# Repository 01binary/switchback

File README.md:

<br>

<br>

<br>

Custom double-neck guitar design with keyboard for playing [neurometal](https://www.youtube.com/playlist?list=PL2ZwTvIdYJGJxl1kszP3a_z6O4DcHwvok).

* 6-string (bottom) modeled after [Strandberg Boden Metal 6](https://strandbergguitars.com/product/boden-metal-6-white-pearl/) with Fishman Fluence Modern 6 pickups
* 8-string (top) modeled after [Strandberg Boden Metal 8](https://www.sweetwater.com/store/detail/BDMT8BKP--strandberg-boden-metal-8-black-pearl) with Fishman Fluence Modern 8 pickups
* 9-key [Roli Seaboard Block keyboard](https://roli.com/products/seaboard) (bottom) with two extra dimensions of touch
* Built-in oscilloscope can display a waveform from a remote synth or sampler, similar to [Korg Minilogue](https://www.sweetwater.com/store/detail/MinilogueXD--korg-minilogue-xd-4-voice-analog-synthesizer)

|Content|In|
|-|-|
|Autodesk Inventor, AutoCAD|./src|
|Concept art and inspiration|./design|
|CAD Drawings|./design/cad|
|3D Renders|./design/render|
|References based on|./references|
|Export to various formats|./export|

<br>

<br>

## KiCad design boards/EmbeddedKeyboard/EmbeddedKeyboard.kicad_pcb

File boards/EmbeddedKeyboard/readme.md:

# Embedded MIDI Keyboard

A PCB embedded at the bottom of a custom guitar, with capacitive touch electrodes that function like keyboard keys. Touching keys sends MIDI messages over Bluetooth.

Each of the `13` keys is divided into `12` electrodes and functions like a capacitive touch slider, allowing the user to slide their finger up and down on each key to control MIDI "brightness" parameter (`CC74`).

> Note that the keyboard is mounted "upside down" for easy access when wearing the guitar.

## Overview

+ All MIDI messages are sent on channel `1`
+ Touching any electrode of a key will send a MIDI `Note On` message with maximum velocity and the note value set according to the key index
+ When touch is no longer registered on a key, the controller will send a MIDI `Note Off` message with minimum velocity
+ The system is strictly **monophonic**:
  - At most one key may be active at any time
  - At most one electrode position is considered active at any time
+ Depending on which key electrode was touched (`0` through `23`), the controller will send a `Control Change` message with controller `74` (or `4AH`, mapped to *brightness* in MIDI specification) and value equal to the index of the key electrode mapped onto `0` through `127` range.

The board outline is provided as an `.svg` export. This includes the shape of the board, hole placement, and the shape of the electrodes:

The capacitive touch electrodes must be placed on one side of the board, and all components on the other.

## Requirements

### General
- All MIDI messages are sent on channel `1`
- MIDI Control Change `CC74` (`0x4A`, Brightness) is always sent when a key is touched or released
- Control Change value is derived from the closest electrode index (`0–11`) mapped linearly to `0–127`

### Touch behavior

#### Case 1: Touch a key when no other key is active

+ Given my finger is over the `C1` key
+ When I touch any electrode within this key
  - Then the controller sends **MIDI Control Change**
    * Channel: `1`
    * Controller: `CC74`
    * Value: `0–127` (mapped from electrode index)
  - Then the controller sends **MIDI Note On**
    * Channel: `1`
    * Pitch: `C1`
    * Velocity: `127`

#### Case 2: Move to another key while holding a key

+ Given I am holding the `C1` key
+ When I touch any electrode within the `C2` key
  - Then the controller sends **MIDI Note Off**
    * Channel: `1`
    * Pitch: `C1`
    * Velocity: `0`
  - Then the controller sends **MIDI Control Change**
    * Channel: `1`
    * Controller: `CC74`
    * Value: `0–127` (mapped from electrode index)
  - Then the controller sends **MIDI Note On**
    * Channel: `1`
    * Pitch: `C2`
    * Velocity: `127`

#### Case 3: Release the active key

+ When I release the active key
  - Then the controller sends **MIDI Control Change**
    * Channel: `1`
    * Controller: `CC74`
    * Value: `0–127`
  - Then the controller sends **MIDI Note Off**
    * Channel: `1`
    * Pitch: last active pitch
    * Velocity: `0`

## Testing

[MIDI Monitor](https://www.snoize.com/MIDIMonitor/) can be used for testing this device once assembled to ensure it adheres to above requirements.

## Architecture

### Controller

The [ESP32-S3-DEVKITC-1-N8](https://www.digikey.com/en/products/detail/espressif-systems/ESP32-S3-DEVKITC-1-N8/15199021) controller was chosen because it can function like a Bluetooth MIDI device, and it's also used for the embedded oscilloscope board in the same project.

The ESP32-S3 shall expose all required GPIO, I²C, UART, boot, and reset signals on the PCB without relying on bodge wires.

### Capacitive Touch

The [MPR121QR2](https://www.digikey.com/en/products/detail/nxp-usa-inc/MPR121QR2/2186527) capacitive touch controller was selected due to its simplicity, reliability, and native I²C interface. Each MPR121 provides **12 capacitive electrodes**, and multiple devices can coexist on the same I²C bus using its **four selectable I²C addresses (0x5A–0x5D)**.

This project requires **13 keys × 12 electrodes per key = 156 total electrodes**, corresponding to **13 MPR121 devices** (1 per key).

To minimize device count, routing complexity, and I²C bus capacitance, the design shall use a **single [TCA9548A](https://www.digikey.com/en/products/detail/texas-instruments/tca9548apwr/3615458) I²C multiplexer**. Each TCA9548A downstream channel may host **up to four MPR121 devices**, differentiated by their I²C addresses. With this approach, all 13 MPR121 devices can be supported using **7 of the 8 available TCA9548A channels**, leaving one channel unused for expansion or debugging.

This architecture is preferred over a "one-sensor-per-mux-channel" approach because it:

- Minimizes the number of multiplexers
- Reduces PCB routing congestion
- Keeps I²C timing deterministic
- Simplifies firmware scanning (each sensor is read once per scan cycle)

Each key shall be treated logically as a **1D capacitive slider**, composed of **12 contiguous electrodes**, with position derived in firmware from the combined electrode state.

> Note: each MPR121 device has an IRQ (interrupt) pin pulled `LOW` when touch is registered.

### Power

This section is a **direct reuse** of a previously validated "Embedded Oscilliscope" design and should not be functionally modified unless required for layout reasons.

A [USB-C](https://www.digikey.com/en/products/detail/hirose-electric-co-ltd/CX90B1-24P/8769505) receptacle is used to program the board, providing power during the programming process. Two [TS-1064S-A1B2-D4](https://www.lcsc.com/product-detail/C498294.html?s_z=n_C498294) switches (boot and reset) are used for manual programming. A [DMN3135LVT-7](https://www.digikey.com/en/products/detail/diodes-incorporated/dmn3135lvt-7/2890874) MOSTFET enables automatic programming from Arduino IDE.

The circuitry from [Adafruit LiPo backpack](https://www.adafruit.com/product/2124) is integrated directly onto the board to provide power from a LiPo battery after the device is programmed. This includes [S2B-PH-SM4-TB](https://www.digikey.com/en/products/detail/jst-sales-america-inc/s2b-ph-sm4-tb/926655) **battery connector** and a **sliding power switch**. If the battery is connected while power is provided to the USB-C connector, this also charges the battery.

The power switch (connected to LiPo Battery Backpack circuit) is **external** for this project - but [S2B-PH-SM4-TB](https://www.digikey.com/en/products/detail/jst-sales-america-inc/s2b-ph-sm4-tb/926655) connector will be needed on the board to connect this external switch in a modular fashion. This is exactly the same connector as the one used for the battery.

The circuitry from [Adafruit LM3671 Buck Converter](https://www.adafruit.com/product/2745) is integrated directly onto the board to convert the battery voltage to `3.3V` required for the controller and all other components.

## Components

|Component|Description|
|-|-|
|[ESP32-WROOM-32E-N4](https://www.lcsc.com/product-detail/C701341.html)|Controller|
|[MCP73831T-2ACI/OT](https://www.digikey.com/en/products/detail/microchip-technology/mcp73831t-2aci-ot/964301)|Battery Charger
|[150080SS75000](https://www.digikey.com/en/products/detail/w-rth-elektronik/150080SS75000/4489919)|Red LED
|[150080GS75000](https://www.digikey.com/en/products/detail/w-rth-elektronik/150080GS75000/4489913)|Green LED
|[RE0805FRE071KL](https://www.digikey.com.au/en/products/detail/yageo/RE0805FRE071KL/5923534)|1K Resistor
|[RC0805FR-072K49L](https://www.digikey.com/en/products/detail/yageo/RC0805FR-072K49L/727695)|2.5K Resistor
|[0402WGF5101TCE](https://www.lcsc.com/product-detail/C25905.html)|5.1K Resistor
|[AF0805FR-0710KL](https://www.digikey.it/en/products/detail/yageo/AF0805FR-0710KL/5901208)|10K Resistor
|[RT0805FRE0775KL](https://www.digikey.com/en/products/detail/yageo/RT0805FRE0775KL/1079396)|75K Resistor
|[RC0805FR-07100KL](https://www.digikey.com/en/products/detail/yageo/RC0805FR-07100KL/727544)|100K Resistor
|[RTT01513JTH](https://www.lcsc.com/product-detail/C102736.html)|51K Resistor
|[0805W8F220JT5E](https://jlcpcb.com/partdetail/18249-0805W8F220JT5E/C17561)|22 Ohm Resistor
|[S2B-PH-SM4-TB](https://www.digikey.com/en/products/detail/jst-sales-america-inc/S2B-PH-SM4-TB/926655)|LiPo Battery Connector, Power Switch Connector
|[CC0805KKX5R5BB106](https://www.digikey.com/en/products/detail/yageo/cc0805kkx5r5bb106/2833624)|10uF Capacitor
|[CC0805MKX5R5BB226](https://www.digikey.com/en/products/detail/yageo/CC0805MKX5R5BB226/2833629)|22uF Capacitor
|[CL03A104KP3NNNC](https://www.digikey.com/en/products/detail/samsung-electro-mechanics/cl03a104kp3nnnc/3886773)|100nF Capacitor
|[LM3671MFX-3.3/NOPB](https://www.digikey.com/en/products/detail/texas-instruments/LM3671MFX-3.3-NOPB/6597333)|3.3V DC-DC Buck Converter
|[NRH2412T2R2MNGH](https://www.digikey.com/en/products/detail/taiyo-yuden/NRH2412T2R2MNGH/4157831)|2.2uH Inductor
|[TS-1064S-A1B2-D4](https://www.lcsc.com/product-detail/C498294.html)|Boot and Reset Switches
|[USB-C31-S-RA-CS2-SMT-BK-T/R](https://www.digikey.com/en/products/detail/adam-tech/USB-C31-S-RA-CS2-SMT-BK-T-R/9833235)|USB-C Receptacle
|[DMN3135LVT-7](https://www.digikey.com/en/products/detail/diodes-incorporated/dmn3135lvt-7/2890874)|ESP32 Auto-program MOSFET
|[CH340C](https://www.lcsc.com/product-detail/C84681.html)|USB to Serial Converter
|[MPR121QR2](https://www.digikey.com/en/products/detail/nxp-usa-inc/mpr121qr2/2186527)|Capacitive Touch Sensor
|[TCA9548APWR](https://www.digikey.com/en/products/detail/texas-instruments/tca9548apwr/3615458)|I2C Multiplexer (Bus Switch)

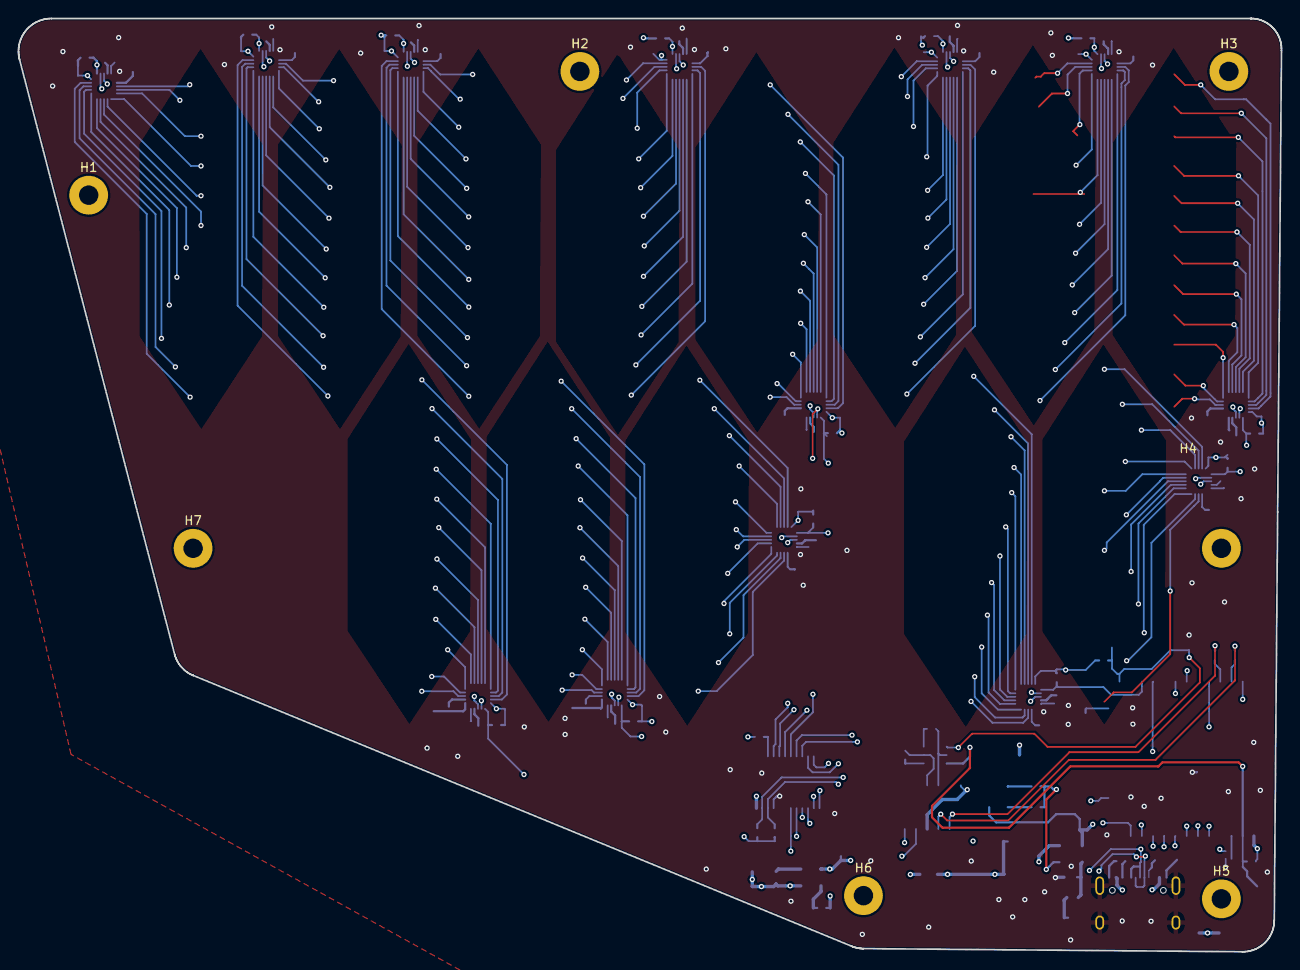
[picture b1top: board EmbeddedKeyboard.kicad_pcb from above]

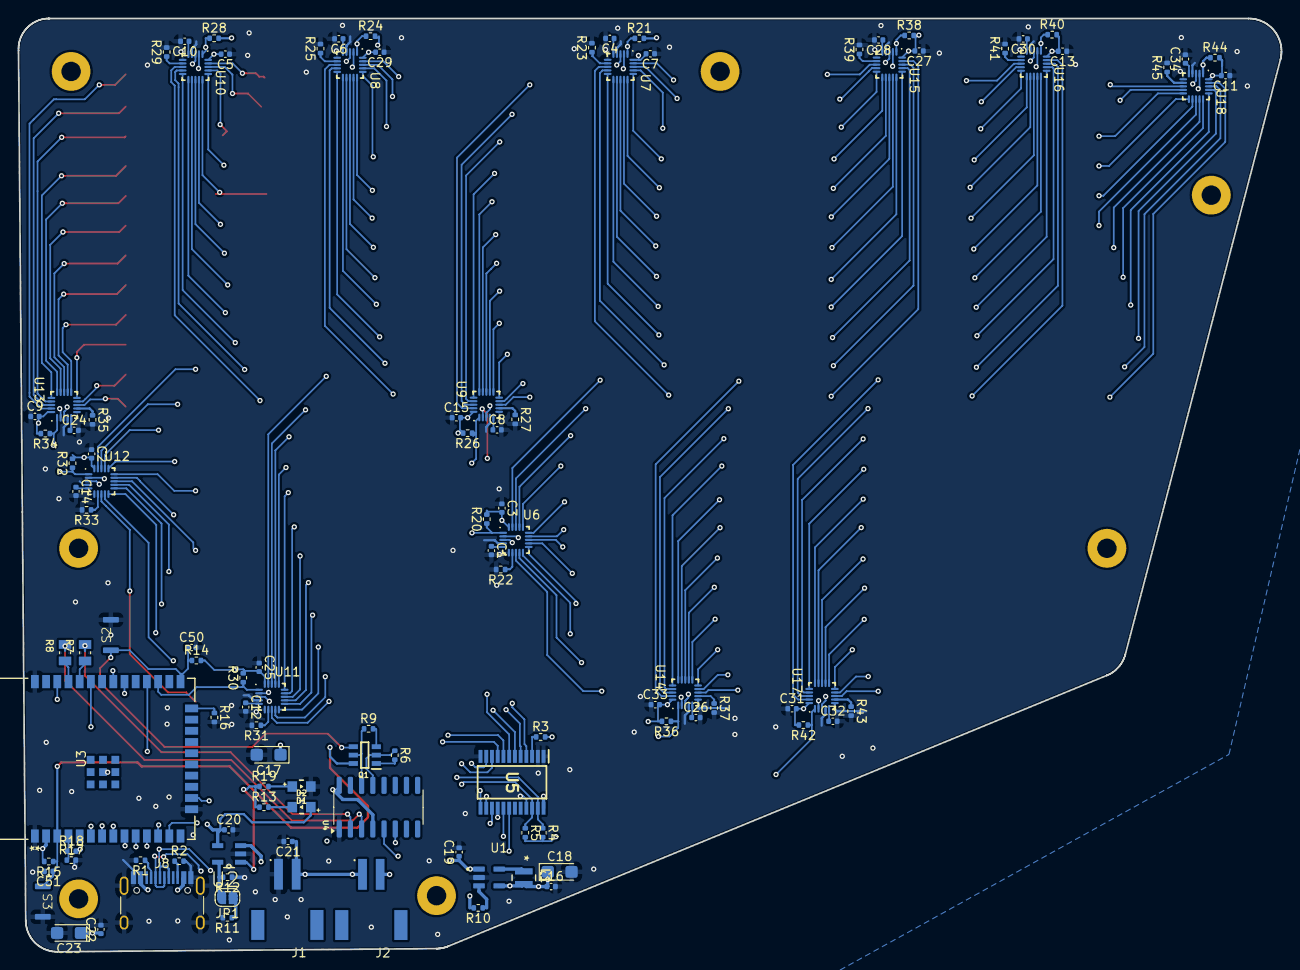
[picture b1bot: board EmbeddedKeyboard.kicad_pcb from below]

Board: 4 copper layers, 143.2 x 105.8 mm, 116 parts (109 on the bottom side), 84 nets.

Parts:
C1, C2, C3, C4, C5, C6, C7, C8, C9, C10, C11, C12, C13, C14, C15, C16, C22, C24, C25, C26, C27, C28, C29, C30, C31, C32, C33, C34, C50, C51: 100nF; C_0402_1005Metric
C17, C18, C23: 10uF; CP_EIA-3216-18_Kemet-A
C19, C20, C21: 10uF; C_0402_1005Metric
D1: GREEN LED (DONE); 150080GS75000
D2: RED LED (CHARGING); 150080SS75000
H1, H2, H3, H4, H5, H6, H7: MountingHole; MountingHole_2.2mm_M2_Pad
J1: S2B-PH-SM4-TB
J2: EXTERNAL SWITCH; S2B-PH-SM4-TB
J8: USB_C_Receptacle_USB2.0_14P; USB_C_Receptacle_HRO_TYPE-C-31-M-12
JP1: SolderJumper; SolderJumper-2_P1.3mm_Open_RoundedPad1.0x1.5mm
L1: 2.2uH; NRH2412T2R2MNGH
Q1: DMN3135LVT-7
R1, R2: 5.1k; R_0402_1005Metric
R3, R4, R5, R6, R9, R12, R14, R15, R16, R20, R21, R24, R26, R28, R30, R32, R34, R36, R38, R40, R42, R44: 10K; R_0402_1005Metric
R7, R8: 22R; 0805W8F220JT5E
R10: 100K; R_0402_1005Metric
R11: 2.5K; R_0402_1005Metric
R13, R19: 1K; R_0402_1005Metric
R17, R18: 51K; R_0402_1005Metric
R22, R23, R25, R27, R29, R31, R33, R35, R37, R39, R41, R43, R45: 75K; R_0402_1005Metric
S2, S3: TS-1064S-A1B2-D4
U1: LM3671MFX-3.3_NOPB; SOT95P280X145-5N
U2: MCP73831T-2ACI_OT; MCP73831T-2ACI-OT
U3: ESP32-WROOM-32E; ESP32-WROOM-32E-N4
U4: CH340C
U5: TCA9548APWR; SOP65P640X120-24N
U6, U7, U8, U9, U10, U11, U12, U13, U14, U15, U16, U17, U18: MPR121QR2

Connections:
+3.3V: C2.2, C3.2, C5.2, C7.2, C9.2, C11.2, C13.2, C15.2, C16.1, C17.1, C18.1, C25.2, C27.2, C29.2, C31.2, C33.2, L1.2, R3.2, R4.2, R5.2, R14.2, R15.2, R20.2, R21.2, R24.2, R26.2, R28.2, R30.2, R32.2, R34.2, R36.2, R38.2, R40.2, R42.2, R44.2, U1.4 (FB), U3.2 (VDD), U4.4 (V3), U4.16 (VCC), U5.24 (VCC), U6.20 (VDD), U7.20 (VDD), U8.20 (VDD), U9.20 (VDD), U10.20 (VDD), U11.20 (VDD), U12.20 (VDD), U13.20 (VDD), U14.20 (VDD), U15.20 (VDD), U16.20 (VDD), U17.20 (VDD), U18.20 (VDD)
+5V: C20.1, C22.1, C23.1, D2.2, J8.A4 (VBUS), J8.A9 (VBUS), J8.B4 (VBUS), J8.B9 (VBUS), U2.4 (VDD)
/Bat: R17.1, R18.1, U3.4 (SENSOR_VP)
/D+: J8.A6 (D+), J8.B6 (D+), U4.5 (UD+)
/D-: J8.A7 (D-), J8.B7 (D-), U4.6 (UD-)
/DTR: Q1.2 (S2), R6.1, U4.13 (~DTR)
/G0: C50.1, Q1.4 (D2), R14.1, S2.1, U3.25 (IO0)
/G2: R16.1, U3.24 (IO2)
/RTS: Q1.5 (S1), R9.1, U4.14 (~RTS)
/Rst: C51.1, Q1.6 (D1), R15.1, S3.1, U3.3 (EN)
/URx: R7.1, U3.34 (RXD0/IO3)
/UTx: R8.1, U3.35 (TXD0/IO1)
GND: C1.2, C2.1, C3.1, C4.2, C5.1, C6.2, C7.1, C8.2, C9.1, C10.2, C11.1, C12.2, C13.1, C14.2, C15.1, C16.2, C17.2, C18.2, C19.2, C20.2, C21.2, C22.2, C23.2, C24.2, C25.1, C26.2, C27.1, C28.2, C29.1, C30.2, C31.1, C32.2, C33.1, C34.2, C50.2, C51.2, D1.1, J1.1, J8.A1 (GND), J8.A12 (GND), J8.B1 (GND), J8.B12 (GND), J8.S1 (SHIELD), R1.2, R2.2, R11.2, R12.1, R16.2, R17.2, R22.2, R23.2, R25.2, R27.2, R29.2, R31.2, R33.2, R35.2, R37.2, R39.2, R41.2, R43.2, R45.2, S2.2, S3.2, U1.2 (GND), U2.2 (VSS), U3.1 (GND), U3.15 (GND), U3.38 (GND), U3.39 (GND), U4.1 (GND), U5.1 (A0), U5.2 (A1), U5.12 (GND), U5.21 (A2), U6.4 (ADDR), U6.6 (VSS), U7.4 (ADDR), U7.6 (VSS), U8.4 (ADDR), U8.6 (VSS), U9.4 (ADDR), U9.6 (VSS), U10.4 (ADDR), U10.6 (VSS), U11.4 (ADDR), U11.6 (VSS), U12.4 (ADDR), U12.6 (VSS), U13.4 (ADDR), U13.6 (VSS), U14.4 (ADDR), U14.6 (VSS), U15.4 (ADDR), U15.6 (VSS), U16.4 (ADDR), U16.6 (VSS), U17.4 (ADDR), U17.6 (VSS), U18.4 (ADDR), U18.6 (VSS)
I2C_RESET_IN: R3.1, U5.3 (*RESET)
IRQ0: R20.1, U3.28 (IO17), U6.1 (~IRQ)
IRQ1: R21.1, U3.12 (IO27), U7.1 (~IRQ)
IRQ2: R24.1, U3.31 (IO19), U8.1 (~IRQ)
IRQ3: R26.1, U3.30 (IO18), U9.1 (~IRQ)
IRQ4: R28.1, U3.8 (IO32), U10.1 (~IRQ)
IRQ5: R30.1, U3.27 (IO16), U11.1 (~IRQ)
IRQ6: R32.1, U3.7 (IO35), U12.1 (~IRQ)
IRQ7: R34.1, U3.6 (IO34), U13.1 (~IRQ)
IRQ8: R36.1, U3.16 (IO13), U14.1 (~IRQ)
IRQ9: R38.1, U3.13 (IO14), U15.1 (~IRQ)
IRQ10: R40.1, U3.11 (IO26), U16.1 (~IRQ)
IRQ11: R42.1, U3.10 (IO25), U17.1 (~IRQ)
IRQ12: R44.1, U3.9 (IO33), U18.1 (~IRQ)
unnamed: D1.2, R19.2
unnamed: D2.1, R13.2
unnamed: J8.A5 (CC1), R1.1
unnamed: J8.B5 (CC2), R2.1
unnamed: JP1.1 (A), R11.1
unnamed: JP1.2 (B), R12.2, U2.5 (PROG)
unnamed: Q1.1 (G1), R6.2
unnamed: Q1.3 (G2), R9.2
unnamed: R10.1, U1.3 (EN)
unnamed: L1.1, U1.5 (SW)
unnamed: R13.1, R19.1, U2.1 (STAT)
unnamed: R8.2, U4.3 (RXD)
unnamed: R7.2, U4.2 (TXD)
unnamed: R22.1, U6.7 (REXT)
unnamed: C1.1, U6.5 (VREG)
unnamed: R23.1, U7.7 (REXT)
unnamed: C4.1, U7.5 (VREG)
unnamed: R25.1, U8.7 (REXT)
unnamed: C6.1, U8.5 (VREG)
unnamed: R27.1, U9.7 (REXT)
unnamed: C8.1, U9.5 (VREG)
unnamed: R29.1, U10.7 (REXT)
unnamed: C10.1, U10.5 (VREG)
unnamed: R31.1, U11.7 (REXT)
unnamed: C12.1, U11.5 (VREG)
unnamed: R33.1, U12.7 (REXT)
unnamed: C14.1, U12.5 (VREG)
unnamed: R35.1, U13.7 (REXT)
unnamed: C24.1, U13.5 (VREG)
unnamed: R37.1, U14.7 (REXT)
unnamed: C26.1, U14.5 (VREG)
unnamed: R39.1, U15.7 (REXT)
unnamed: C28.1, U15.5 (VREG)
unnamed: R41.1, U16.7 (REXT)
unnamed: C30.1, U16.5 (VREG)
unnamed: R43.1, U17.7 (REXT)
unnamed: C32.1, U17.5 (VREG)
unnamed: R45.1, U18.7 (REXT)
unnamed: C34.1, U18.5 (VREG)
SCL0: U5.5 (SC0), U6.2 (SCL), U7.2 (SCL)
SCL1: U5.7 (SC1), U8.2 (SCL), U9.2 (SCL)
SCL2: U5.9 (SC2), U10.2 (SCL), U11.2 (SCL)
SCL3: U5.11 (SC3), U12.2 (SCL), U13.2 (SCL)
SCL4: U5.14 (SC4), U14.2 (SCL), U15.2 (SCL)
SCL5: U5.16 (SC5), U16.2 (SCL), U17.2 (SCL)
SCL6: U5.18 (SC6), U18.2 (SCL)
SCL_IN: R5.1, U3.36 (IO22), U5.22 (SCL)
SDA0: U5.4 (SD0), U6.3 (SDA), U7.3 (SDA)
SDA1: U5.6 (SD1), U8.3 (SDA), U9.3 (SDA)
SDA2: U5.8 (SD2), U10.3 (SDA), U11.3 (SDA)
SDA3: U5.10 (SD3), U12.3 (SDA), U13.3 (SDA)
SDA4: U5.13 (SD4), U14.3 (SDA), U15.3 (SDA)
SDA5: U5.15 (SD5), U16.3 (SDA), U17.3 (SDA)
SDA6: U5.17 (SD6), U18.3 (SDA)
SDA_IN: R4.1, U3.33 (IO21), U5.23 (SDA)
VB+: C21.1, J1.2, J2.1, U2.3 (VBAT)
VBo+: C19.1, J2.2, R10.2, R18.2, U1.1 (VIN)

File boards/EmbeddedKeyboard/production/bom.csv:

Designator,Footprint,Quantity,Value,LCSC Part #
"C1, C10, C11, C12, C13, C14, C15, C16, C2, C22, C24, C25, C26, C27, C28, C29, C3, C30, C31, C32, C33, C34, C4, C5, C50, C51, C6, C7, C8, C9",0402,30,100nF,C1525 
"C17, C18, C23",CP_EIA-3216-18_Kemet-A,3,10uF,C7171
"C19, C20, C21",0402,3,10uF,C77000
D1,150080GS75000,1,GREEN LED (DONE),C12624
D2,150080SS75000,1,RED LED (CHARGING),C2286
J1,S2B-PH-SM4-TB,1,S2B-PH-SM4-TB,C51940124
J2,S2B-PH-SM4-TB,1,EXTERNAL SWITCH,C51940124
J8,USB_C_Receptacle_HRO_TYPE-C-31-M-12,1,USB_C_Receptacle_USB2.0_14P,C165948 
L1,NRH2412T2R2MNGH,1,2.2uH,C89149 
Q1,DMN3135LVT-7,1,DMN3135LVT-7,C155326 
"R1, R2",0402,2,5.1k,C25905 
R10,0402,1,100K,C25741
R11,0402,1,2.5K,C25884
"R12, R14, R15, R16, R20, R21, R24, R26, R28, R3, R30, R32, R34, R36, R38, R4, R40, R42, R44, R5, R6, R9",0402,22,10K,C25744
"R13, R19",0402,2,1K,C11702
"R17, R18",0402,2,51K,C25794 
"R22, R23, R25, R27, R29, R31, R33, R35, R37, R39, R41, R43, R45",0402,13,75K,C25798
"R7, R8",0402,2,22R,C17561 
"S2, S3",TS-1064S-A1B2-D4,2,TS-1064S-A1B2-D4,C498294
U1,SOT95P280X145-5N,1,LM3671MFX-3.3_NOPB,C477918
"U10, U11, U12, U13, U14, U15, U16, U17, U18, U6, U7, U8, U9",MPR121QR2,13,MPR121QR2,C91322
U2,MCP73831T-2ACI-OT,1,MCP73831T-2ACI_OT,C424093
U3,ESP32-WROOM-32E-N4,1,ESP32-WROOM-32E,C328062 
U4,CH340C,1,CH340C,C84681
U5,SOP65P640X120-24N,1,TCA9548APWR,C130026

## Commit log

2018-01-20 Initial concepts
2018-01-20 Update images add specs
2018-01-20 Add 9-string specs
2018-01-20 Add references
2018-01-28 Developing vector outline
2018-01-28 Finalize outline 2
2018-01-30 Updated and exported outline2
2018-03-26 Adjust outline2
2019-05-31 add more designs
2019-06-01 Last updates before CAD
2019-12-05 Updated after sending to 3D CNC
2019-12-29 another iteration after proto
2019-12-30 Add drawings and 3D
2019-12-30 Update exports
2019-12-30 Export with dimensions
2020-01-15 parts, assembly, more refs and design
2020-01-15 separated wood pieces
2020-01-16 divide and fillets
2020-01-17 add todo
2020-01-17 add neck profiles
2020-01-17 verify neck mounts and lofts
2020-01-19 Defined neck mounts more
2020-01-19 head and neck detailing
2020-01-21 Adding block
2020-01-21 seaboard detail
2020-01-21 finished seaboard, repairing body
2020-01-22 redoing compartments
2020-01-23 block ifeatures
2020-01-23 working on cavities again:
2020-01-25 more work on compartments
2020-01-25 redoing control mounts
2020-01-28 Revalidate after indent adjustment
2020-01-28 Lengthened neck bases
2020-01-28 Update gitignore to add lock file
2020-01-28 Updated todo
2020-01-30 Attempting to redo seaboard
2020-01-30 Finished keyboard
2020-01-31 Finished neck base
2020-01-31 Update todo
2020-02-01 Block mount detail
2020-02-01 Block mount more detailing
2020-02-02 Cover indents
2020-02-02 Separated osc cover
2020-02-03 Finalized cover draft and redid tuners
2020-02-04 Redo logo
2020-02-05 Drawing views
2020-02-06 Repairing neck, renders
2020-02-06 renders
2020-02-08 Add drawings
2020-02-08 edit front page
2020-02-08 Readme diagrams
2020-02-08 Working on guide
2020-02-10 Finalize guide
2020-03-24 Add notes
2020-09-30 Pieces for booleans
2020-12-25 Osc code
2021-03-18 Build pics
2021-09-06 Export handles and update readme
2021-09-06 Extension typo
2021-09-28 Updated embedded oscilloscope
2021-09-30 Changes for bluetooth
2021-11-30 Sunrom doc and remove notes
2022-11-01 Update handles based on latest body
2022-11-01 Redo handles
2023-08-29 Tail and keyboard patterns
2024-09-18 Recent design experiments
2025-12-08 Add boards
2025-12-09 Cleanup
2025-12-09 Correct typo
2025-12-09 PDF from readme
2025-12-09 Updated for new architecture agreed upon for Fiverr quote
2025-12-09 Re-generated readme with project deliverables
2025-12-10 Sourced all components
2025-12-10 Oscilloscope symbol library
2025-12-10 Buck converter and battery backpack
2025-12-20 Cleaning up MIDI keyboard requirements
2025-12-20 Minor edits
2025-12-20 Normalize requirements
2025-12-20 Edit cap touch section
2025-12-21 Getting requirements together
2025-12-21 Files no longer needed
2025-12-21 More unneeded files
2025-12-21 More cleanup on requirements
2025-12-21 Power switch detail
2025-12-21 More edits
2025-12-21 Under construction warning
2025-12-22 Board outline
2025-12-23 Embedded oscilloscope Fiverr delivery
2025-12-23 Finish component list
2025-12-23 Board outline has electrodes sectioned
2025-12-23 Small note
2025-12-23 Update firmware to latest
2025-12-23 Rename firmware folders
2025-12-23 Update board outline for dark mode
2025-12-23 Start off project with osc board
2025-12-29 Enough spec to communicate intent
2025-12-29 Note about interrupts
2026-02-03 Update embedded keyboard schematic for 12 segments
2026-02-03 Minor cleanup
2026-02-03 Clean up board outline again
2026-02-03 Final pre-submission
2026-02-03 Unlock files
2026-02-03 Remove captured readme
2026-02-20 Re-designed keyboard
2026-02-20 Switch out 22 Ohm resistor 0603 > 0805
